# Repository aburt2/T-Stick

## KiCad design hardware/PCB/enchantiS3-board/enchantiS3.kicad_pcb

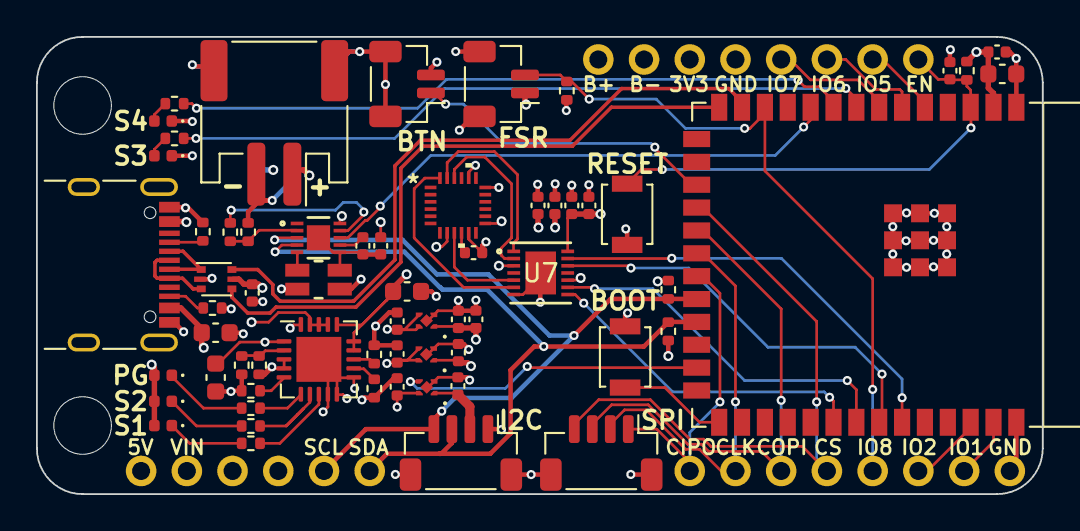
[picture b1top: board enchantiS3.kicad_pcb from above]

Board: 4 copper layers, 55.9 x 25.4 mm, 66 parts (1 on the bottom side), 59 nets.

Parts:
ANG1, ANG2: JST-SH-1.00mm 1x2; JST_SH_BM02B-SRSS-TB_1x02-1MP_P1.00mm_Vertical
BOARDLAYOUT1: LAYOUT; board-layout
BT1, BT2: JST-PH-1x02-2.000mm; JST_PH_S2B-PH-SM4-TB_1x02-1MP_P2.00mm_Horizontal
C1, C6, C7, C15, C18, C19, C21: 0.1uF; C_0402_1005Metric
C2: 0.47uF; C_0402_1005Metric
C3, C8: 4.7uF; C_0603_1608Metric
C4, C5, C9, C10, C11, C12, C16, C17, C20: 1uF; C_0402_1005Metric
C13, C14: 10uF; C_0603_1608Metric
CHARGLED1: S1; LED_0402_1005Metric
CHARGLED2: S2; LED_0402_1005Metric
CHARGLED3: PG; LED_0402_1005Metric
FG1: MAX17055ETB+T; 21-100013A_T102A2&plus_1C_MXM
H1, H2: MountingHole; MountingHole_3.2mm_M3_DIN965
IMU1: ICM-20948; QFN24_3X3X0P9_IVS
J1: USB_C_Receptacle_USB2.0; USB_C_Receptacle_GCT_USB4105-xx-A_16P_TopMnt_Horizontal
MCU1: ESP32-S3-WROOM-2
R1, R3, R8, R10, R22, R24: 1k; R_0402_1005Metric
R2: Ohmite_LVK12 10m; LVK12_OHM-L
R4: 110k; R_0402_1005Metric
R5, R9, R12: 10k; R_0402_1005Metric
R6, R7: 5k1; R_0402_1005Metric
R16, R19: 2k2; R_0402_1005Metric
R17: 24.9k; R_0402_1005Metric
R18: 330k; R_0402_1005Metric
R20: 2k; R_0402_1005Metric
STATLED1: WIFISTATUS; LED_0402_1005Metric
STATLED2: GENERAL STATUS; LED_0402_1005Metric
SW1, SW2: B3U-1000P; SW_SPST_B3U-1000P
TH1: 10k; R_0402_1005Metric
TOUCH1, TOUCH2: JST-SH-1x04 1.0mm; JST_SH_BM04B-SRSS-TB_1x04-1MP_P1.00mm_Vertical
U1: USBLC6-2P6; SOT-666
U2: MCP73871; QFN-20-1EP_4x4mm_P0.5mm_EP2.5x2.5mm
U3, U5: NCP167AMX330TBG; XDFN4_1X1_711AJ_ONS
U4: NCP167AMX180TBG; XDFN4_1X1_711AJ_ONS
U7: max3378eetd+t; 21-0137I_T1433-2_MXM

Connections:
+1V8: C7.1, C10.1, C12.1, C18.1, IMU1.8 (VDDIO), IMU1.13 (VDD), U4.1 (OUT), U7.3 (*THREE-STATE), U7.10 (VL)
+3V3: ANG1.1, BOARDLAYOUT1.1.3 (3v3), BOARDLAYOUT1.3.3 (3v3), C5.1, C13.1, C19.1, C20.1, C21.1, MCU1.2 (3V3), R5.2, R16.2, R19.2, U3.1 (OUT), U7.14 (VCC)
+3V3_AUX: C16.1, TOUCH1.2, U5.1 (OUT)
+BATT: BOARDLAYOUT1.1.1 (VBAT), BT1.1, BT2.1, C1.1, C8.1, FG1.10 (BATT), U2.14 (V_{BAT}), U2.15 (V_{BAT}), U2.16 (V_{BAT_SENSE})
-BATT: BOARDLAYOUT1.1.2 (BATGND), BT1.2, BT2.2, R2.1, TH1.2
/AIN: FG1.2 (AIN), R12.1, TH1.1
/CIPO: BOARDLAYOUT1.2.1 (CS), MCU1.21 (GPIO13/TOUCH13/ADC2_CH2/FSPIQ/FSPIIO7/S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), TOUCH2.1
/CIPO_1V8: IMU1.9 (SDO/AD0), U7.5 (I/O_VL3)
/CIPO_AUX: MCU1.33 (MTDO/GPIO40/CLK_OUT2), U7.9 (I/O_VCC3)
/CLK_1V8: IMU1.23 (SCL/SCLK), U7.1 (I/O_VL1)
/CLK_AUX: MCU1.35 (MTMS/GPIO42), U7.13 (I/O_VCC1)
/COPI: BOARDLAYOUT1.2.3 (SCLK), MCU1.19 (GPIO11/TOUCH11/ADC2_CH0/FSPID/FSPIIO5/S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), TOUCH2.3
/COPI_1V8: IMU1.24 (SDA/SDI), U7.6 (I/O_VL4)
/COPI_AUX: MCU1.32 (MTCK/GPIO39/CLK_OUT3/SUBSPICS1), U7.8 (I/O_VCC4)
/CS: BOARDLAYOUT1.2.4 (COPI), MCU1.18 (GPIO10/TOUCH10/ADC1_CH9/FSPICS0/FSPIIO4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), TOUCH2.4
/CS_1V8: IMU1.22 (~CS), U7.2 (I/O_VL2)
/CS_AUX: MCU1.34 (MTDI/GPIO41/CLK_OUT1), U7.12 (I/O_VCC2)
/D+: J1.A6 (D+), J1.B6 (D+), U1.3 (I/O2)
/D-: J1.A7 (D-), J1.B7 (D-), U1.1 (I/O1)
/EN: BOARDLAYOUT1.1.8 (EN), C9.1, MCU1.3 (EN), R5.1, SW2.1
/FG_CSN: FG1.5 (CSN), R2.3
/IO0: MCU1.27 (GPIO0/BOOT), SW1.1
/IO1: BOARDLAYOUT1.2.7 (A3), MCU1.39 (GPIO1/TOUCH1/ADC1_CH0)
/IO2: BOARDLAYOUT1.2.6 (A2), MCU1.38 (GPIO2/TOUCH2/ADC1_CH1)
/IO5: BOARDLAYOUT1.1.7 (A6), MCU1.5 (GPIO5/TOUCH5/ADC1_CH4)
/IO6: BOARDLAYOUT1.1.6 (A5), MCU1.6 (GPIO6/TOUCH6/ADC1_CH5)
/IO7: BOARDLAYOUT1.1.5 (A4), MCU1.7 (GPIO7/TOUCH7/ADC1_CH6)
/IO8: ANG1.2, BOARDLAYOUT1.2.5 (A1), MCU1.12 (GPIO8/TOUCH8/ADC1_CH7/SUBSPICS1), R1.1
/IO9: ANG2.1, MCU1.17 (GPIO9/TOUCH9/ADC1_CH8/FSPIHD/SUBSPIHD)
/IO15: MCU1.8 (GPIO15/U0RTS/ADC2_CH4/XTAL_32K_P), R8.1
/IO16: MCU1.9 (GPIO16/U0CTS/ADC2_CH5/XTAL_32K_N), R10.1
/IO17: FG1.8 (ALRT), MCU1.10 (GPIO17/U1TXD/ADC2_CH6)
/LDO_EN: MCU1.25 (GPIO48/SPICLK_N/SUBSPICLK_N_DIFF), U5.3 (EN)
/PG: R24.2, U2.6 (~PG)
/PROG1: R20.2, U2.13 (PROG1)
/PROG3: R17.2, U2.12 (PROG3)
/REG: C2.1, FG1.7 (REG)
/SCL: BOARDLAYOUT1.3.5 (SCL), FG1.3 (SCL), MCU1.22 (GPIO14/TOUCH14/ADC2_CH3/FSPIWP/FSPIDQS/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), R19.1, TOUCH1.4
/SCLK: BOARDLAYOUT1.2.2 (CIPO), MCU1.20 (GPIO12/TOUCH12/ADC2_CH1/FSPICLK/FSPIIO6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), TOUCH2.2
/SDA: BOARDLAYOUT1.3.6 (SDA), FG1.4 (SDA), MCU1.23 (GPIO21), R16.1, TOUCH1.3
/STAT: R3.2, U2.8 (STAT1/~LBO)
/STAT2: R22.2, U2.7 (STAT2)
/THERM: R9.2, U2.5 (THERM)
/THRM: FG1.9 (THRM), R12.2
/USBD+: MCU1.14 (GPIO20/U1CTS/ADC2_CH9/CLK_OUT1/USB_D+), U1.4 (I/O2)
/USBD-: MCU1.13 (GPIO19/U1RTS/ADC2_CH8/CLK_OUT2/USB_D-), U1.6 (I/O1)
/VPCC: R4.2, R18.1, U2.2 (VPCC)
CSP: C1.2, C2.2, FG1.6 (CSP), FG1.11 (EPAD), R2.2
GND: ANG1.MP (MountPin), ANG2.2, ANG2.MP (MountPin), BOARDLAYOUT1.1.4 (GND), BOARDLAYOUT1.2.8 (GND), BOARDLAYOUT1.3.4 (GND), BT1.MP (MountPin), BT2.MP (MountPin), C3.2, C4.2, C5.2, C6.2, C7.2, C8.2, C9.2, C10.2, C11.2, C12.2, C13.2, C14.2, C15.2, C16.2, C17.2, C18.2, C19.2, C20.2, C21.2, IMU1.11 (FSYNC), IMU1.18 (GND), IMU1.20 (GND), J1.A1 (GND), J1.A12 (GND), J1.B1 (GND), J1.B12 (GND), J1.S1 (SHIELD), MCU1.1 (GND), MCU1.40 (GND), MCU1.41 (GND), R1.2, R2.4, R4.1, R6.1, R7.1, R9.1, R17.1, R20.1, STATLED1.1 (K), STATLED2.1 (K), SW1.2, SW2.2, TOUCH1.1, TOUCH1.MP (MountPin), TOUCH2.MP (MountPin), U1.2 (GND), U2.9 (~TE), U2.10 (V_{SS}), U2.11 (V_{SS}), U2.21 (V_{SS}), U3.2 (GND), U3.5 (GND), U4.2 (GND), U4.5 (GND), U5.2 (GND), U5.5 (GND), U7.7 (GND), U7.15 (EPAD)
unnamed: CHARGLED1.1 (K), R3.1
unnamed: CHARGLED2.1 (K), R22.1
unnamed: CHARGLED3.1 (K), R24.1
unnamed: C6.1, IMU1.10 (REGOUT)
unnamed: J1.A5 (CC1), R7.2
unnamed: J1.B5 (CC2), R6.2
unnamed: R8.2, STATLED1.2 (A)
unnamed: R10.2, STATLED2.2 (A)
SYS: BOARDLAYOUT1.3.2 (SYS), C3.1, C4.1, C11.1, C17.1, U2.1 (OUT), U2.20 (OUT), U3.3 (EN), U3.4 (IN), U4.3 (EN), U4.4 (IN), U5.4 (IN)
VUSB: BOARDLAYOUT1.3.1 (5v), C14.1, C15.1, CHARGLED1.2 (A), CHARGLED2.2 (A), CHARGLED3.2 (A), J1.A4 (VBUS), J1.A9 (VBUS), J1.B4 (VBUS), J1.B9 (VBUS), R18.2, U1.5 (VBUS), U2.3 (SEL), U2.4 (PROG2), U2.17 (CE), U2.18 (IN), U2.19 (IN)

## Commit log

2022-04-04 added template maintenance docs
2023-05-24 add suppport for second trill board, send entire trill boar for sopranos
2023-05-24 add support for two full trill boards
2023-07-12 added basic sensor management functionality
2023-07-13 added sensor class, changed all the other specific sensor classes to be a child class of sensor class, added imu sensor class
2023-07-17 add task scheduler library from torquetuner, fixed bugs with i2c conversion
2023-07-18 try to troubleshoot ADC2 errors
2023-07-18 reverted changes to fsr and button classes, added regular I2C scan, fixed crashes related to fsr and puara gestures
2023-07-18 set I2C to high speed mode, included some task scheduling parameters to measure timing
2023-07-18 split up sensor tasks, changed get SensorData so it only gets data from one sensor
2023-07-19 added battery read from T-Stick if no fuel gauge
2023-07-19 split up long tasks into smaller tasks
2023-07-24 split OSC and libmapper tasks
2023-07-24 got osc working, no faster pausing work to focus on hardware
2023-09-28 added fuel gauge
2023-10-19 settings to test trill sensitivity
2023-10-23 changed trill parameters
2023-11-13 revert back to before merge
2023-11-16 move 3d models from 4GW to their own model
2023-11-21 updated 3d models
2023-11-26 updated stabilzer
2023-11-27 split endcap into different files for my sanity
2023-11-28 add new 3d printing files
2024-01-24 updated schematic, added symbol for and gate
2024-01-24 removed, neopixel library, added extra LDO for peripherals
2024-01-25 updated schematic
2024-01-25 updated text in schematic
2024-01-28 added setting memory, default is already max
2024-01-30 upadated schematic, connected IMU data pins to SPI line, updated manufacturing files
2024-01-31 updated BOM and manufacturing files
2024-02-03 moved touch.h
2024-12-09 restructured imu, fuel gauge and touch classes to be based on virtual classes, isolate gpio pins to reduce deep sleep current draw
2024-12-09 added additional comments
2024-12-09 added dev environment
2024-12-09 updated isolation pins for the enchantiS3rev4
2024-12-14 addreading imu from enchantis3 revision 4 board
2024-12-23 add osc helper to edit bundle rather then recreate it every loop
2024-12-27 add magnetomer calibration, cleanup imu utils)
2024-12-28 only normalise pitch and roll to 0-360 degrees
2024-12-28 flip x axis
2024-12-28 remove non public function
2024-12-28 fix axis orientation of the magnetometer and accelerometer
2025-09-02 added IMU class for magnetometer, updated espidf to v5.5 and arduino core v3, added initial support for npm1300 pmic
    puara serial monitor still broken, magnetometer not working
2025-09-02 Added delay to ensure the USB current limit is properly set, removed unused items from tstick presets, print out vbus current limit, remove debug options from platformio
2025-09-03 moved a majority of headers to t-stick-presets.h, added interrupt polling for IMU and Magnetometer
2025-09-03 tried changing GPIO pins (no dice), fixed up the way I'm initiating SPI classes, magnetometer works over I2C
2025-09-03 changed initialisation of SPI bus for magnetomer (still doesn't work)
